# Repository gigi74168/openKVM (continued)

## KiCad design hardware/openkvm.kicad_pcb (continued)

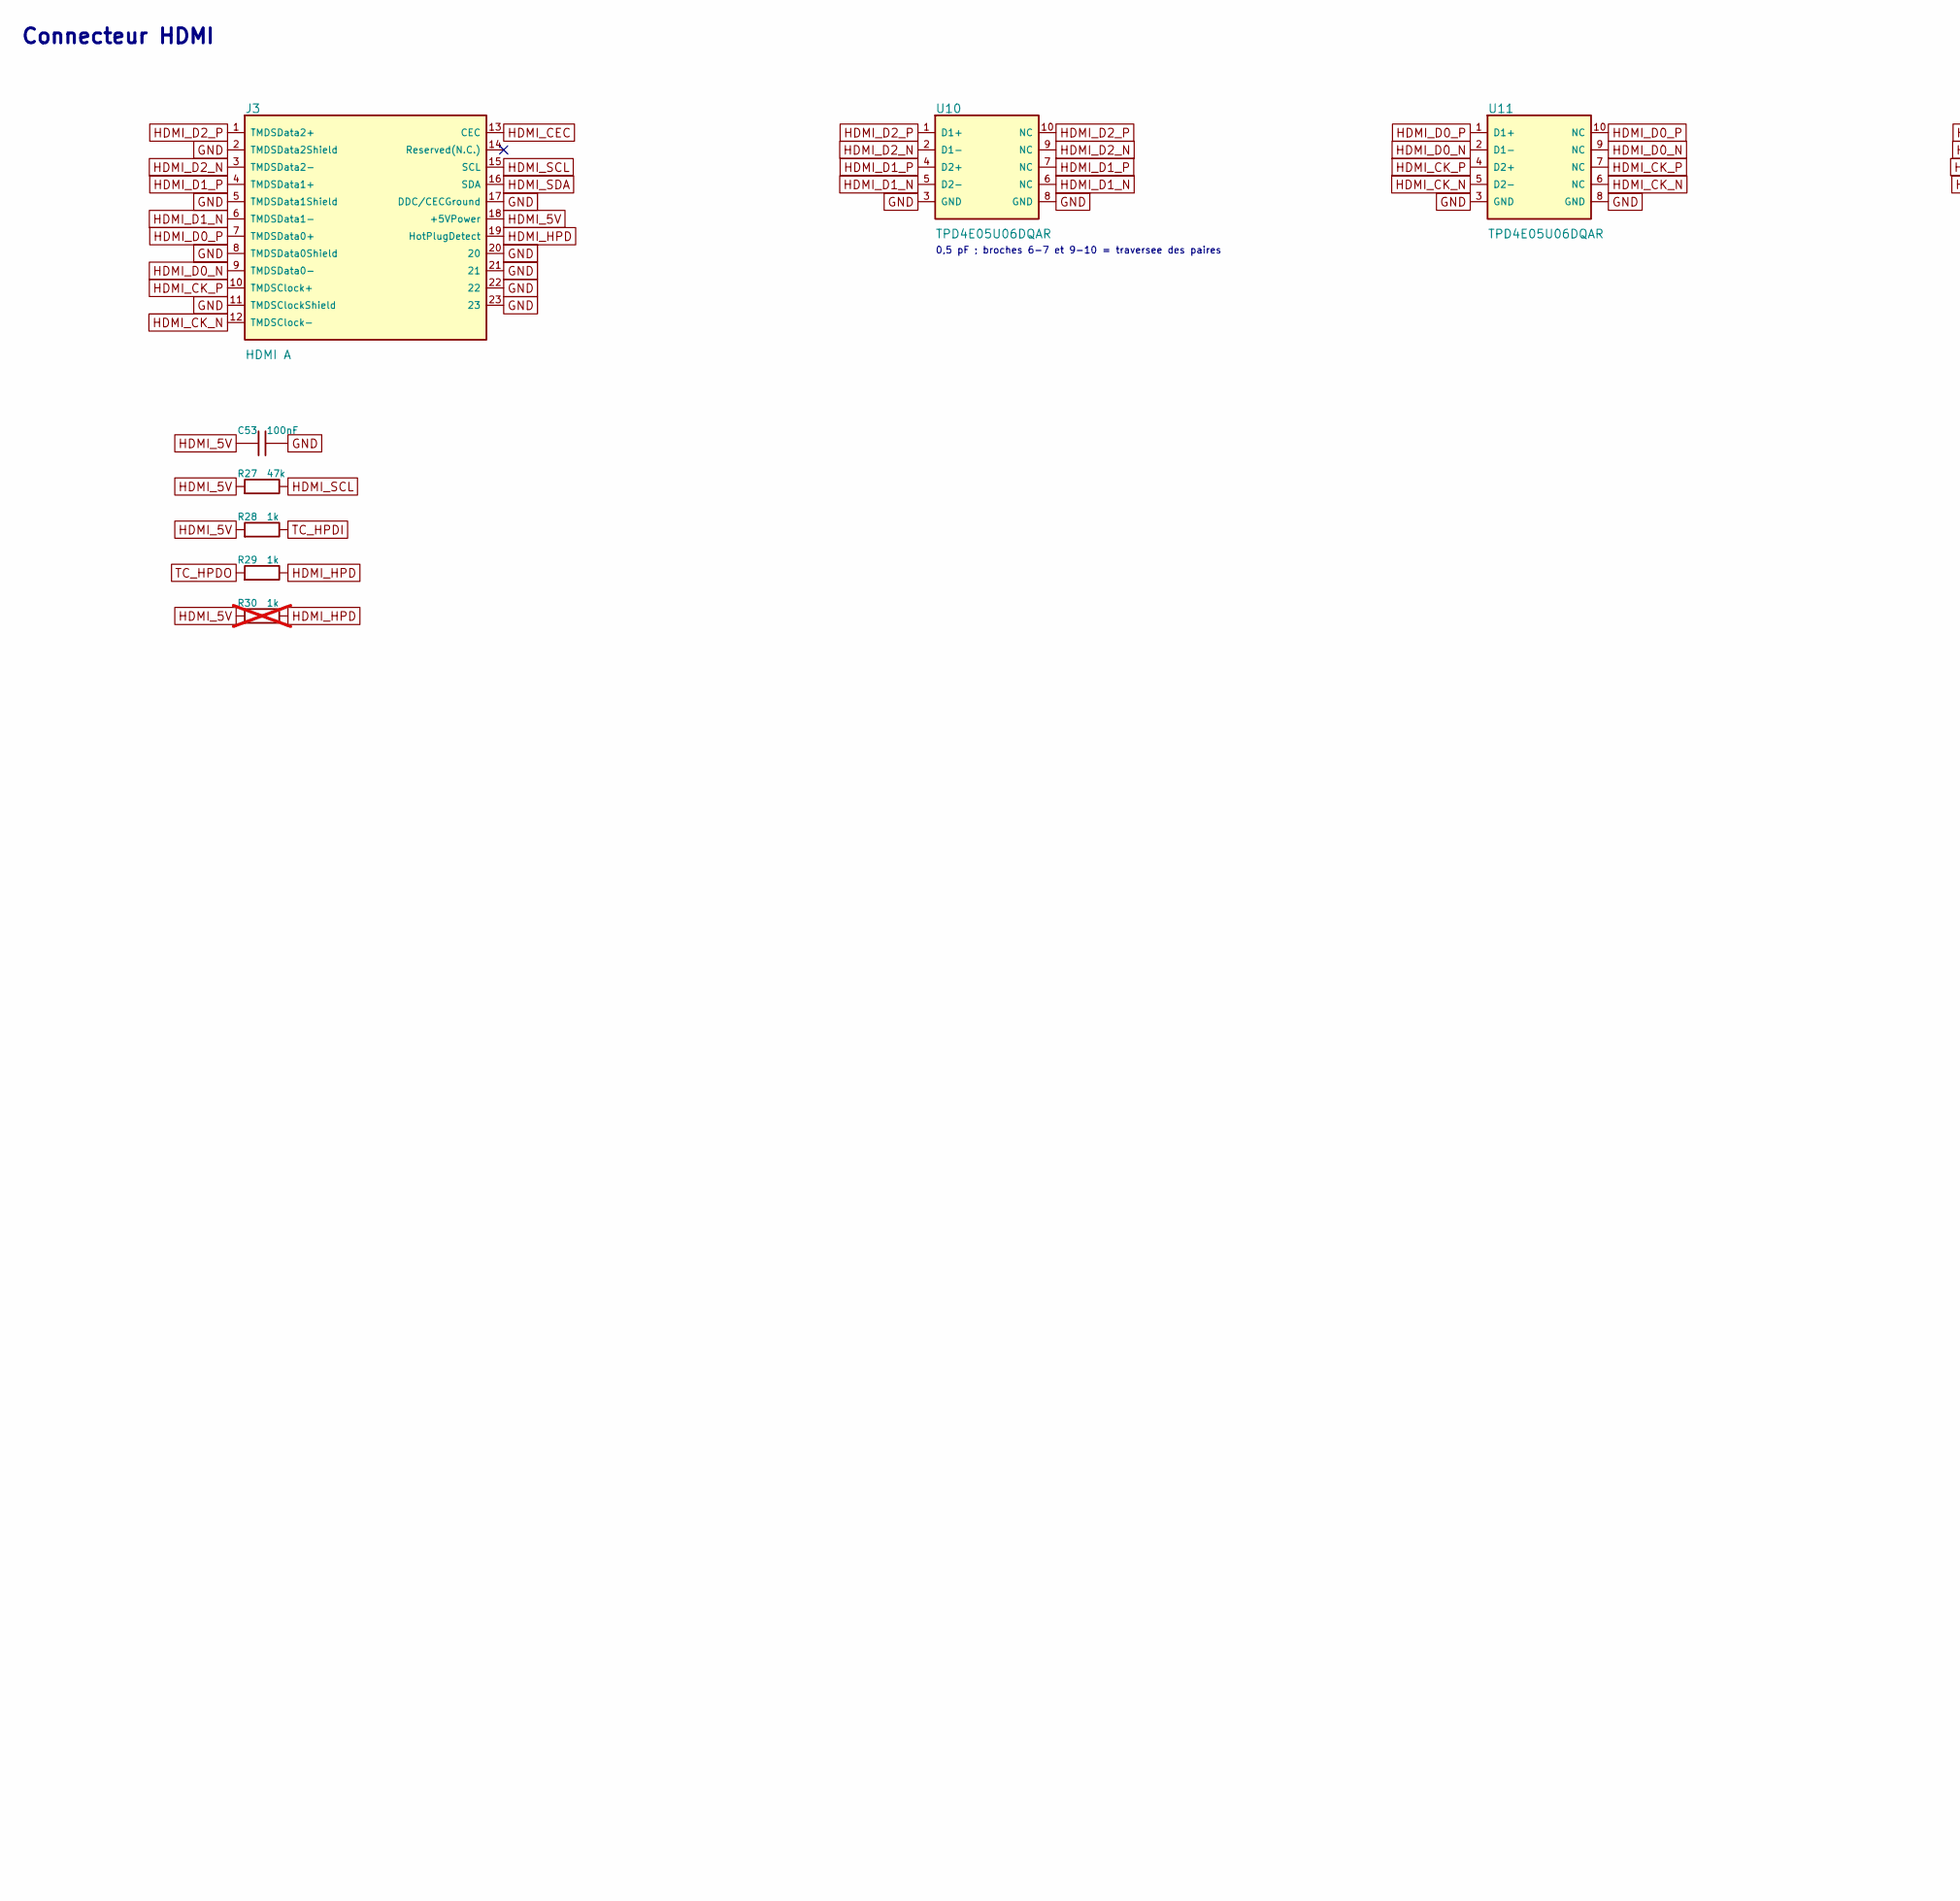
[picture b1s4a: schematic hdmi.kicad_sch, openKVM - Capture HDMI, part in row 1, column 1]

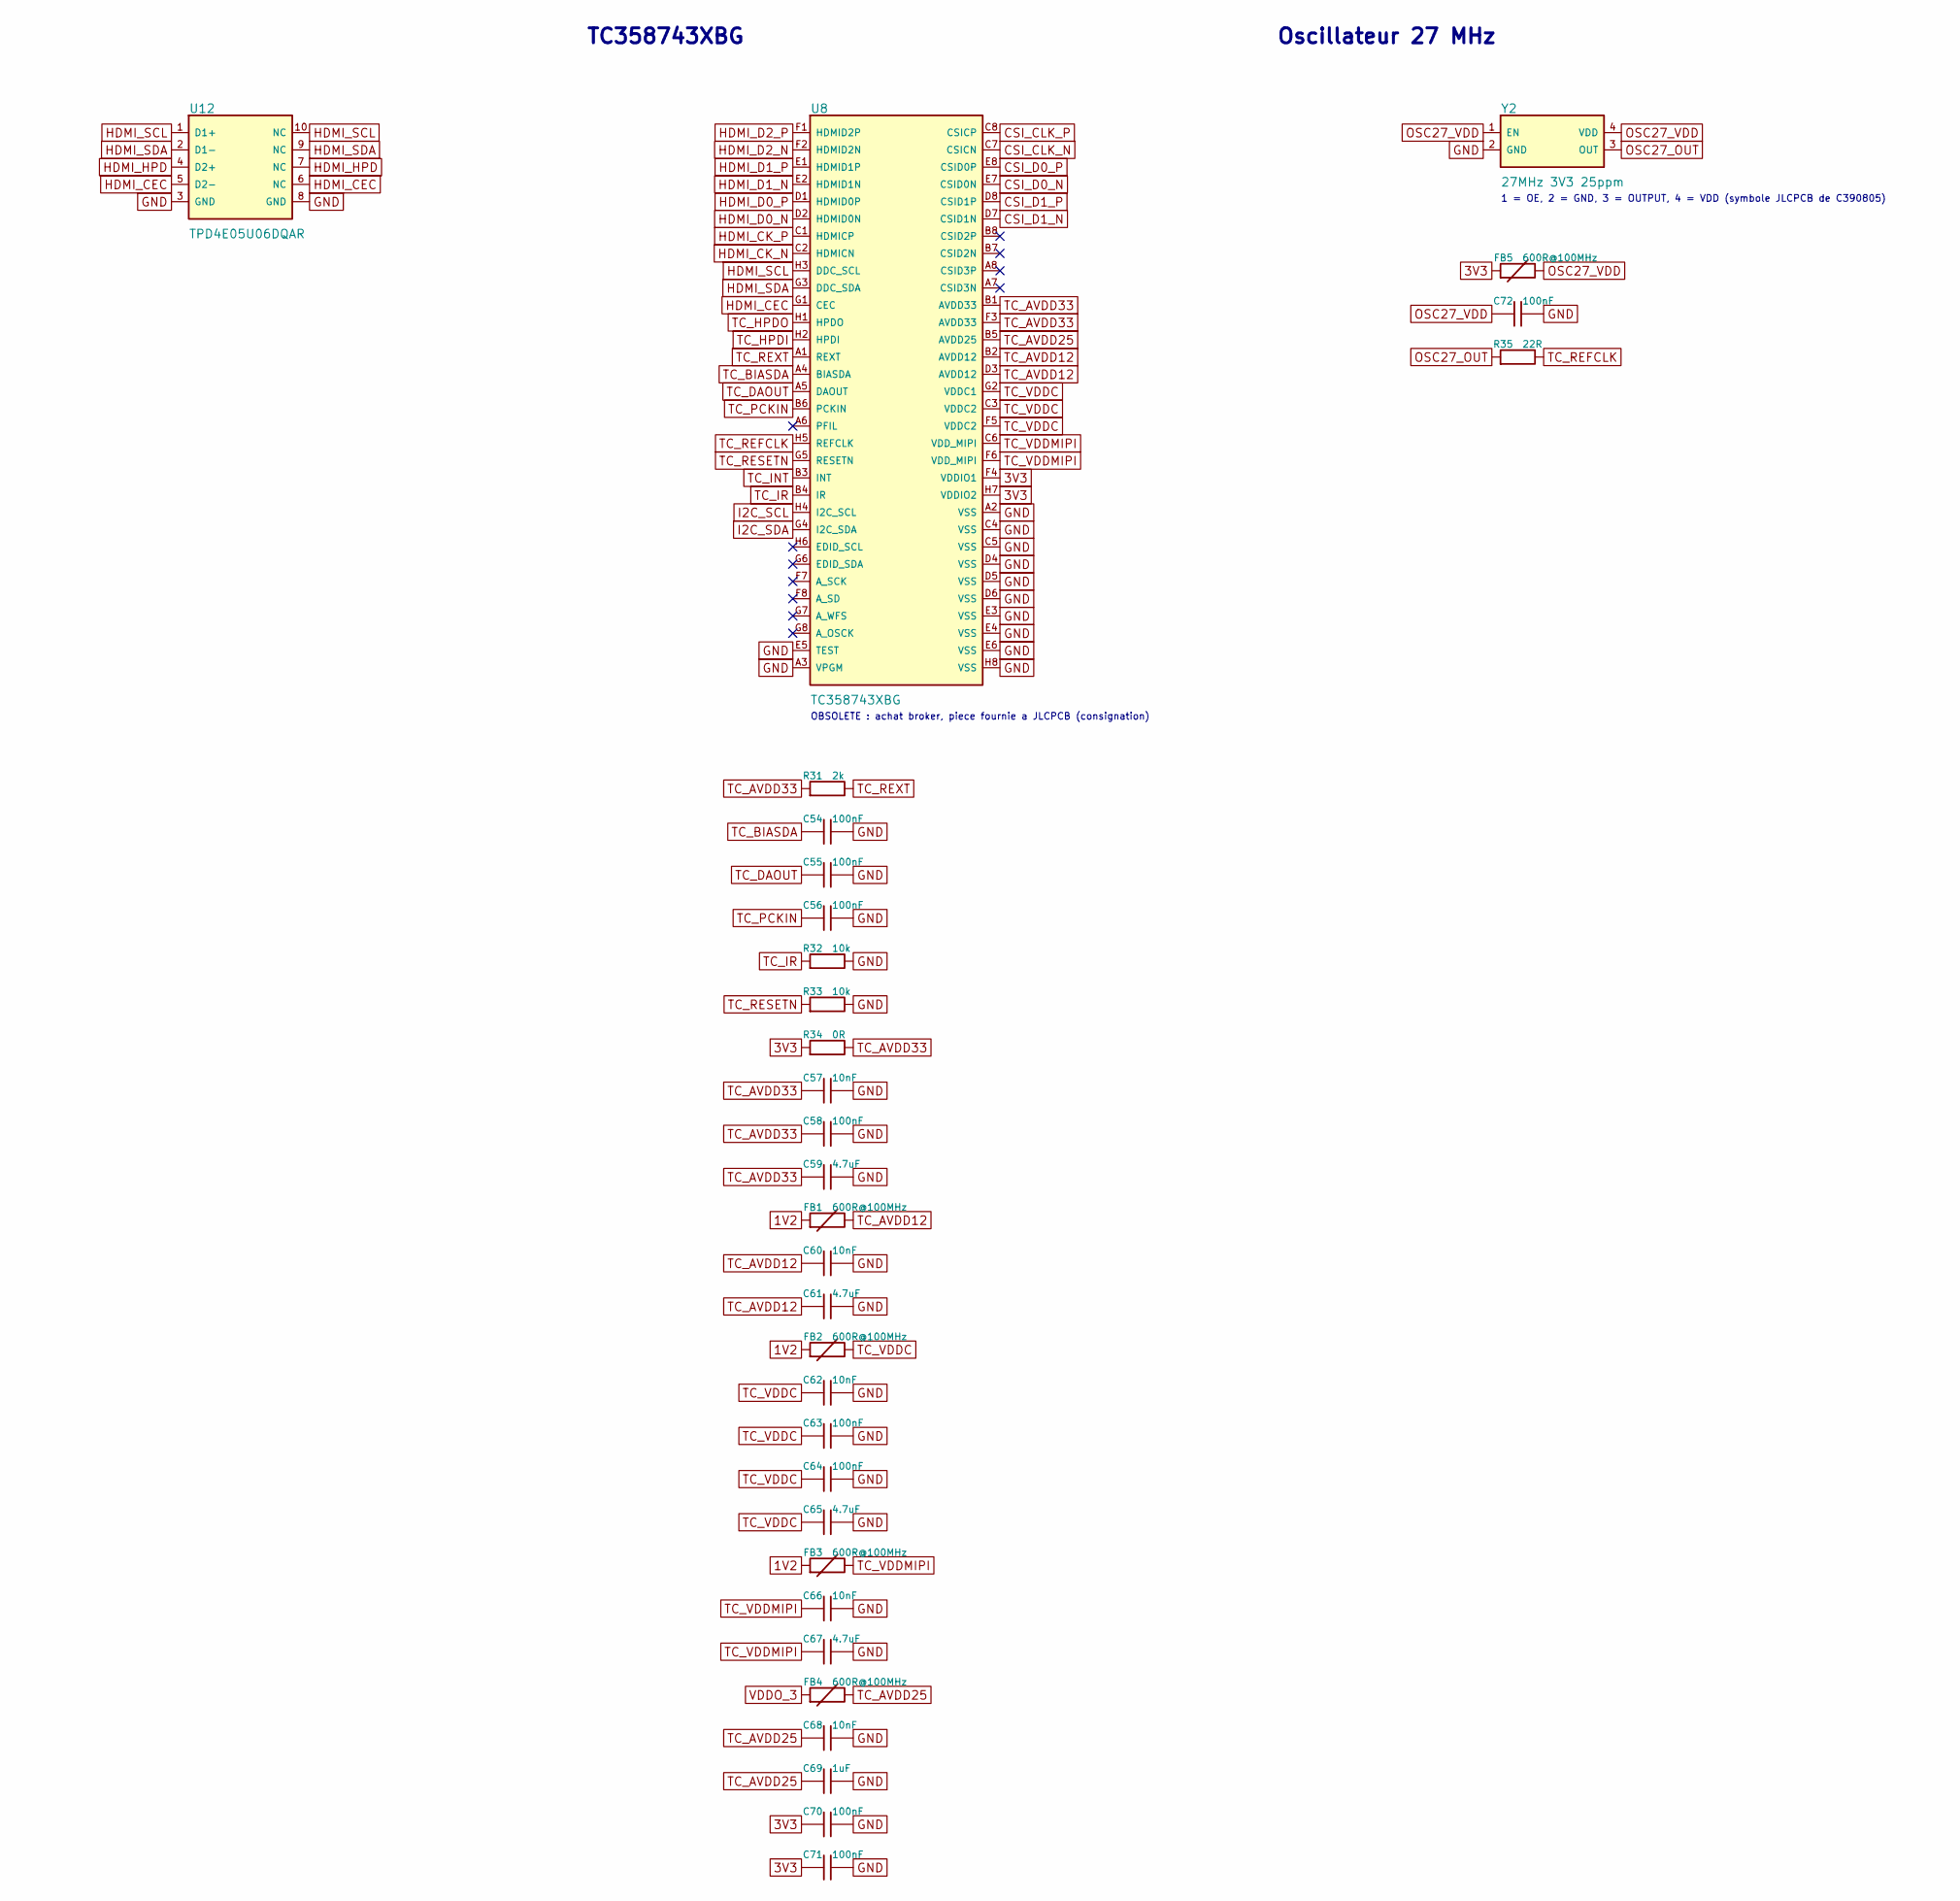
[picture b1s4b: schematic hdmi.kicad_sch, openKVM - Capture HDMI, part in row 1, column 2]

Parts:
C53, C54, C55, C56, C58, C63, C64, C70, C71, C72: 100nF; C_0402_1005Metric; MPN CL05B104KO5NNNC; LCSC C1525
C57, C60, C62, C66, C68: 10nF; C_0402_1005Metric; MPN CL05B103KB5NNNC; LCSC C15195
C59, C61, C65, C67: 4.7uF; C_0603_1608Metric; MPN CL10A475KO8NNNC; LCSC C19666
C69: 1uF; C_0402_1005Metric; MPN CL05A105KA5NQNC; LCSC C52923
FB1, FB2, FB3, FB4, FB5: 600R@100MHz; L_0603_1608Metric; MPN BLM18KG601SN1D; LCSC C85833
J3: HDMI A; HDMI-SMD_19P-P0.50-H-F; MPN HDMI-001 19PCBTP; LCSC C138388
R27: 47k; R_0402_1005Metric; MPN 0402WGF4702TCE; LCSC C25792
R28, R29: 1k; R_0402_1005Metric; MPN 0402WGF1001TCE; LCSC C11702
R30: 1k; R_0402_1005Metric; MPN 0402WGF1001TCE; LCSC C11702; not fitted
R31: 2k; R_0402_1005Metric; MPN 0402WGF2001TCE; LCSC C4109
R32, R33: 10k; R_0402_1005Metric; MPN 0402WGF1002TCE; LCSC C25744
R34: 0R; R_0402_1005Metric; MPN 0402WGF0000TCE; LCSC C17168
R35: 22R; R_0402_1005Metric; MPN 0402WGF220JTCE; LCSC C25092
U8: TC358743XBG; BGA-64_8x8_6.0x6.0mm; MPN TC358743XBG
U10, U11, U12: TPD4E05U06DQAR; USON-10_L2.5-W1.0-P0.50-BL; MPN TPD4E05U06DQAR; LCSC C138714
Y2: 27MHz 3V3 25ppm; OSC-SMD_4P-L3.2-W2.5-BL; MPN O3227000153350; LCSC C390805

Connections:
1V2: FB1.1, FB2.1, FB3.1; also elsewhere on the board
3V3: C70.1, C71.1, FB5.1, R34.1, U8.F4 (VDDIO1), U8.H7 (VDDIO2); also elsewhere on the board
CSI_CLK_N: U8.C7 (CSICN); also elsewhere on the board
CSI_CLK_P: U8.C8 (CSICP); also elsewhere on the board
CSI_D0_N: U8.E7 (CSID0N); also elsewhere on the board
CSI_D0_P: U8.E8 (CSID0P); also elsewhere on the board
CSI_D1_N: U8.D7 (CSID1N); also elsewhere on the board
CSI_D1_P: U8.D8 (CSID1P); also elsewhere on the board
GND: C53.2, C54.2, C55.2, C56.2, C57.2, C58.2, C59.2, C60.2, C61.2, C62.2, C63.2, C64.2, C65.2, C66.2, C67.2, C68.2, C69.2, C70.2, C71.2, C72.2, J3.2 (TMDSData2Shield), J3.5 (TMDSData1Shield), J3.8 (TMDSData0Shield), J3.11 (TMDSClockShield), J3.17 (DDC/CECGround), J3.20, J3.21, J3.22, J3.23, R32.2, R33.2, U8.A2 (VSS), U8.A3 (VPGM), U8.C4 (VSS), U8.C5 (VSS), U8.D4 (VSS), U8.D5 (VSS), U8.D6 (VSS), U8.E3 (VSS), U8.E4 (VSS), U8.E5 (TEST), U8.E6 (VSS), U8.H8 (VSS), U10.3 (GND), U10.8 (GND), U11.3 (GND), U11.8 (GND), U12.3 (GND), U12.8 (GND), Y2.2 (GND); also elsewhere on the board
HDMI_5V: C53.1, J3.18 (+5VPower), R27.1, R28.1, R30.1
HDMI_CEC: J3.13 (CEC), U8.G1 (CEC), U12.5 (D2-), U12.6 (NC)
HDMI_CK_N: J3.12 (TMDSClock-), U8.C2 (HDMICN), U11.5 (D2-), U11.6 (NC)
HDMI_CK_P: J3.10 (TMDSClock+), U8.C1 (HDMICP), U11.4 (D2+), U11.7 (NC)
HDMI_D0_N: J3.9 (TMDSData0-), U8.D2 (HDMID0N), U11.2 (D1-), U11.9 (NC)
HDMI_D0_P: J3.7 (TMDSData0+), U8.D1 (HDMID0P), U11.1 (D1+), U11.10 (NC)
HDMI_D1_N: J3.6 (TMDSData1-), U8.E2 (HDMID1N), U10.5 (D2-), U10.6 (NC)
HDMI_D1_P: J3.4 (TMDSData1+), U8.E1 (HDMID1P), U10.4 (D2+), U10.7 (NC)
HDMI_D2_N: J3.3 (TMDSData2-), U8.F2 (HDMID2N), U10.2 (D1-), U10.9 (NC)
HDMI_D2_P: J3.1 (TMDSData2+), U8.F1 (HDMID2P), U10.1 (D1+), U10.10 (NC)
HDMI_HPD: J3.19 (HotPlugDetect), R29.2, R30.2, U12.4 (D2+), U12.7 (NC)
HDMI_SCL: J3.15 (SCL), R27.2, U8.H3 (DDC_SCL), U12.1 (D1+), U12.10 (NC)
HDMI_SDA: J3.16 (SDA), U8.G3 (DDC_SDA), U12.2 (D1-), U12.9 (NC)
I2C_SCL: U8.H4 (I2C_SCL); also elsewhere on the board
I2C_SDA: U8.G4 (I2C_SDA); also elsewhere on the board
OSC27_OUT: R35.1, Y2.3 (OUT)
OSC27_VDD: C72.1, FB5.2, Y2.1 (EN), Y2.4 (VDD)
TC_AVDD12: C60.1, C61.1, FB1.2, U8.B2 (AVDD12), U8.D3 (AVDD12)
TC_AVDD25: C68.1, C69.1, FB4.2, U8.B5 (AVDD25)
TC_AVDD33: C57.1, C58.1, C59.1, R31.1, R34.2, U8.B1 (AVDD33), U8.F3 (AVDD33)
TC_BIASDA: C54.1, U8.A4 (BIASDA)
TC_DAOUT: C55.1, U8.A5 (DAOUT)
TC_HPDI: R28.2, U8.H2 (HPDI)
TC_HPDO: R29.1, U8.H1 (HPDO)
TC_INT: U8.B3 (INT); also elsewhere on the board
TC_IR: R32.1, U8.B4 (IR)
TC_PCKIN: C56.1, U8.B6 (PCKIN)
TC_REFCLK: R35.2, U8.H5 (REFCLK)
TC_RESETN: R33.1, U8.G5 (RESETN); also elsewhere on the board
TC_REXT: R31.2, U8.A1 (REXT)
TC_VDDC: C62.1, C63.1, C64.1, C65.1, FB2.2, U8.C3 (VDDC2), U8.F5 (VDDC2), U8.G2 (VDDC1)
TC_VDDMIPI: C66.1, C67.1, FB3.2, U8.C6 (VDD_MIPI), U8.F6 (VDD_MIPI)
VDDO_3: FB4.1; also elsewhere on the board

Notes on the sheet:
Connecteur HDMI
0,5 pF ; broches 6-7 et 9-10 = traversee des paires
TC358743XBG
OBSOLETE : achat broker, piece fournie a JLCPCB (consignation)
Oscillateur 27 MHz
1 = OE, 2 = GND, 3 = OUTPUT, 4 = VDD (symbole JLCPCB de C390805)

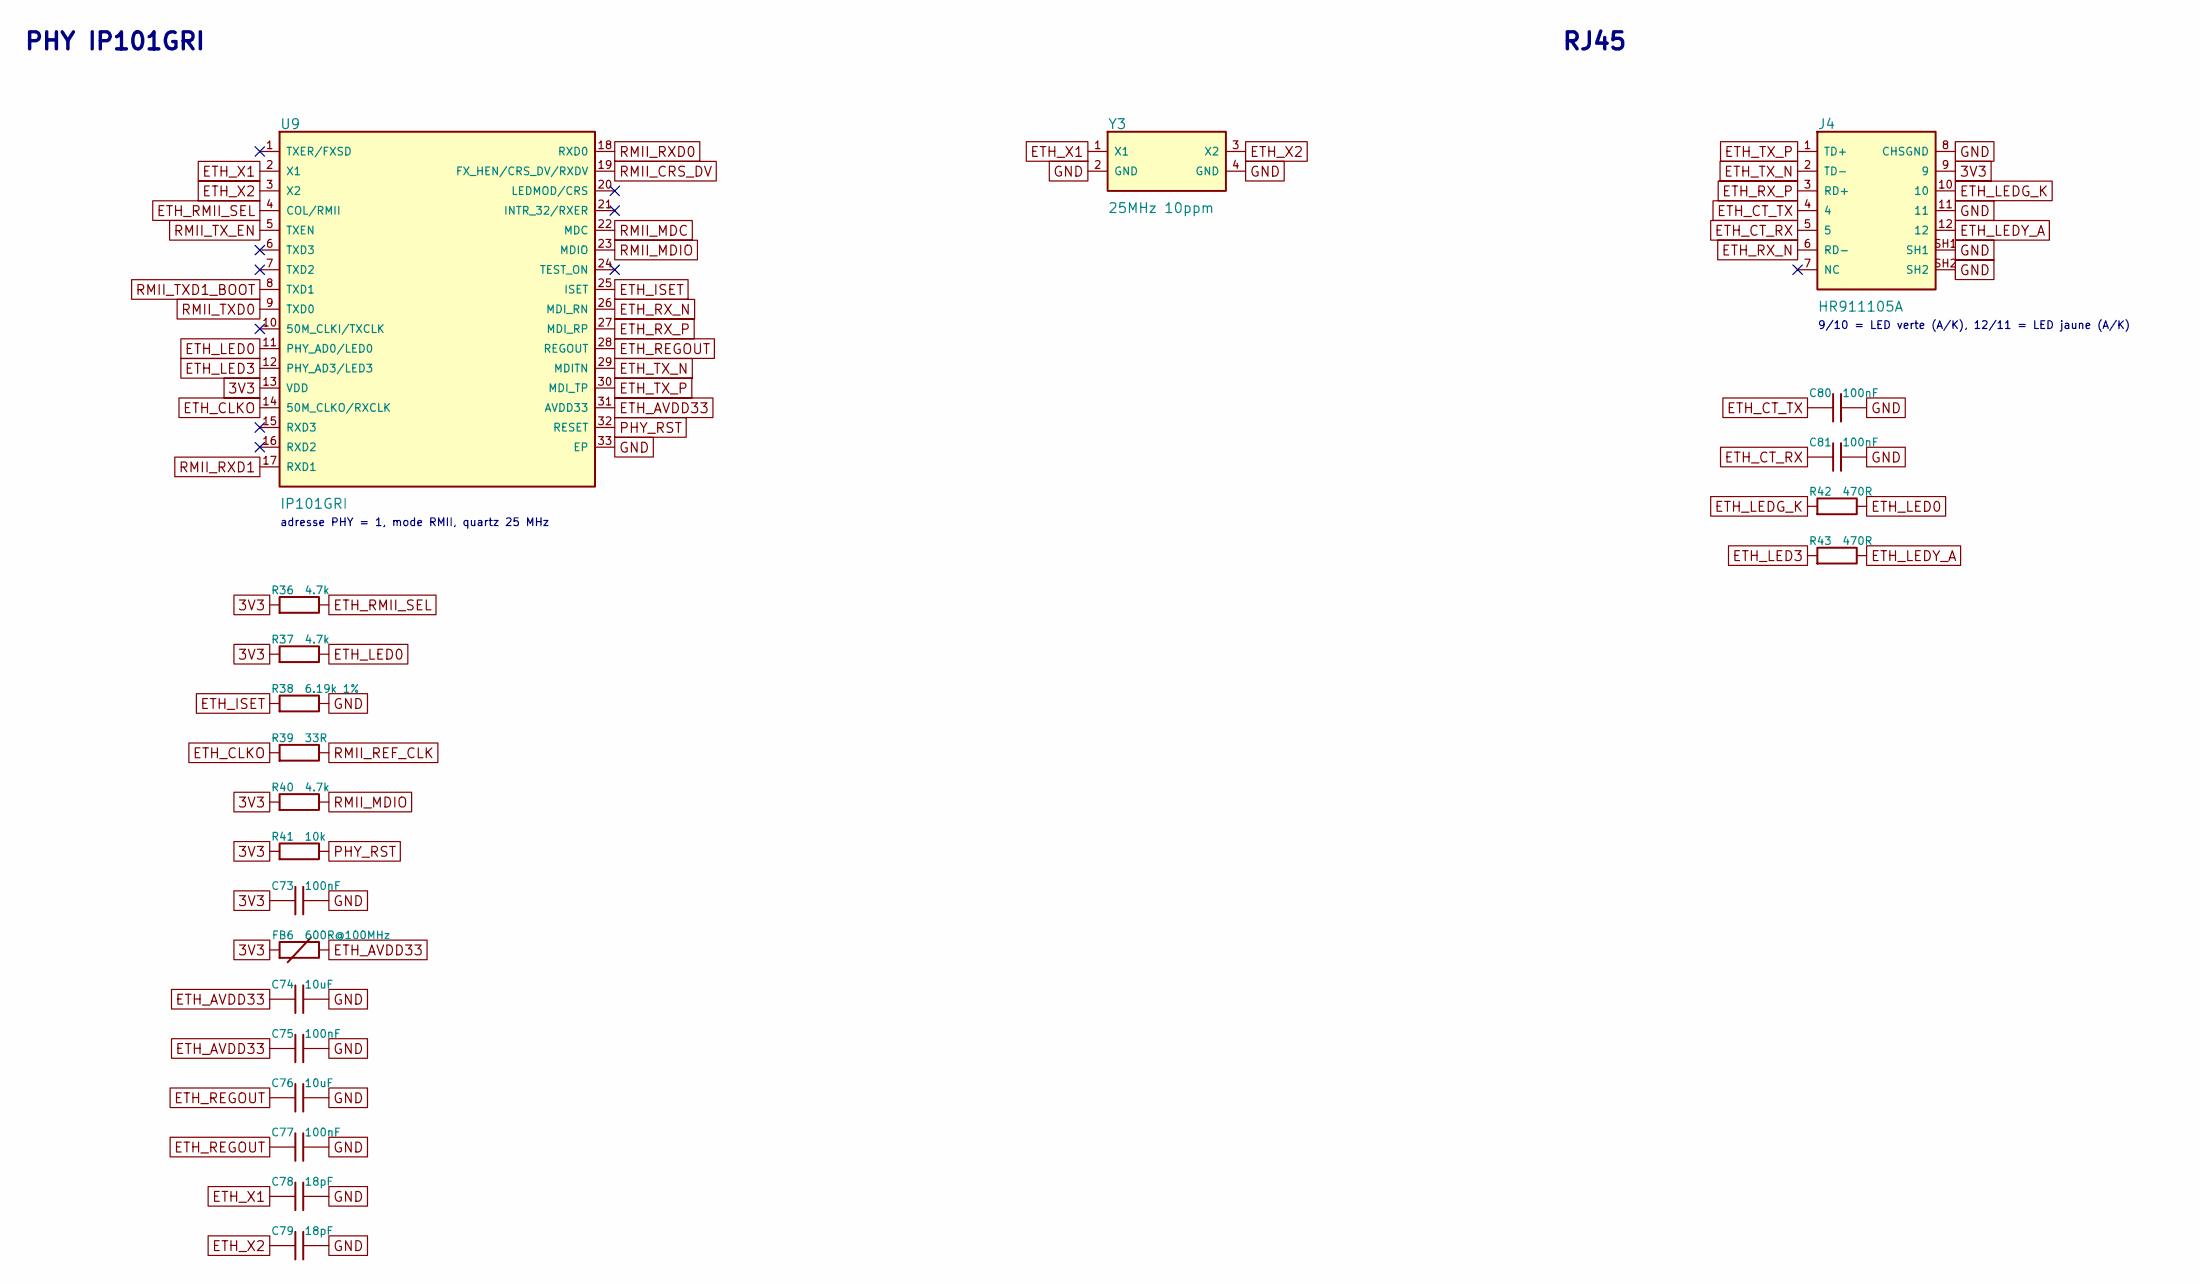
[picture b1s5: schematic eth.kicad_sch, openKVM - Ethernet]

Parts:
C73, C75, C77, C80, C81: 100nF; C_0402_1005Metric; MPN CL05B104KO5NNNC; LCSC C1525
C74, C76: 10uF; C_0603_1608Metric; MPN CL10A106KP8NNNC; LCSC C19702
C78, C79: 18pF; C_0402_1005Metric; MPN 0402CG180J500NT; LCSC C1549
FB6: 600R@100MHz; L_0603_1608Metric; MPN BLM18KG601SN1D; LCSC C85833
J4: HR911105A; RJ45-TH_HR911105A; MPN HR911105A; LCSC C12074
R36, R37, R40: 4.7k; R_0402_1005Metric; MPN 0402WGF4701TCE; LCSC C25900
R38: 6.19k 1%; R_0402_1005Metric; MPN 0402WGF6191TCE; LCSC C25914
R39: 33R; R_0402_1005Metric; MPN 0402WGF330JTCE; LCSC C25105
R41: 10k; R_0402_1005Metric; MPN 0402WGF1002TCE; LCSC C25744
R42, R43: 470R; R_0402_1005Metric; MPN 0402WGF4700TCE; LCSC C25117
U9: IP101GRI; QFN-32_L4.0-W4.0-P0.40-BL-EP2.7; MPN IP101GRI; LCSC C703537
Y3: 25MHz 10ppm; CRYSTAL-SMD_4P-L3.2-W2.5-BL; MPN X322525MOB4SI; LCSC C9006

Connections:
3V3: C73.1, FB6.1, J4.9, R36.1, R37.1, R40.1, R41.1, U9.13 (VDD); also elsewhere on the board
ETH_AVDD33: C74.1, C75.1, FB6.2, U9.31 (AVDD33)
ETH_CLKO: R39.1, U9.14 (50M_CLKO/RXCLK)
ETH_CT_RX: C81.1, J4.5
ETH_CT_TX: C80.1, J4.4
ETH_ISET: R38.1, U9.25 (ISET)
ETH_LED0: R37.2, R42.2, U9.11 (PHY_AD0/LED0)
ETH_LED3: R43.1, U9.12 (PHY_AD3/LED3)
ETH_LEDG_K: J4.10, R42.1
ETH_LEDY_A: J4.12, R43.2
ETH_REGOUT: C76.1, C77.1, U9.28 (REGOUT)
ETH_RMII_SEL: R36.2, U9.4 (COL/RMII)
ETH_RX_N: J4.6 (RD-), U9.26 (MDI_RN)
ETH_RX_P: J4.3 (RD+), U9.27 (MDI_RP)
ETH_TX_N: J4.2 (TD-), U9.29 (MDITN)
ETH_TX_P: J4.1 (TD+), U9.30 (MDI_TP)
ETH_X1: C78.1, U9.2 (X1), Y3.1 (X1)
ETH_X2: C79.1, U9.3 (X2), Y3.3 (X2)
GND: C73.2, C74.2, C75.2, C76.2, C77.2, C78.2, C79.2, C80.2, C81.2, J4.8 (CHSGND), J4.11, J4.SH1, J4.SH2, R38.2, U9.33 (EP), Y3.2 (GND), Y3.4 (GND); also elsewhere on the board
PHY_RST: R41.2, U9.32 (RESET); also elsewhere on the board
RMII_CRS_DV: U9.19 (FX_HEN/CRS_DV/RXDV); also elsewhere on the board
RMII_MDC: U9.22 (MDC); also elsewhere on the board
RMII_MDIO: R40.2, U9.23 (MDIO); also elsewhere on the board
RMII_REF_CLK: R39.2; also elsewhere on the board
RMII_RXD0: U9.18 (RXD0); also elsewhere on the board
RMII_RXD1: U9.17 (RXD1); also elsewhere on the board
RMII_TXD0: U9.9 (TXD0); also elsewhere on the board
RMII_TXD1_BOOT: U9.8 (TXD1); also elsewhere on the board
RMII_TX_EN: U9.5 (TXEN); also elsewhere on the board

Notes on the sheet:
PHY IP101GRI
adresse PHY = 1, mode RMII, quartz 25 MHz
RJ45
9/10 = LED verte (A/K), 12/11 = LED jaune (A/K)

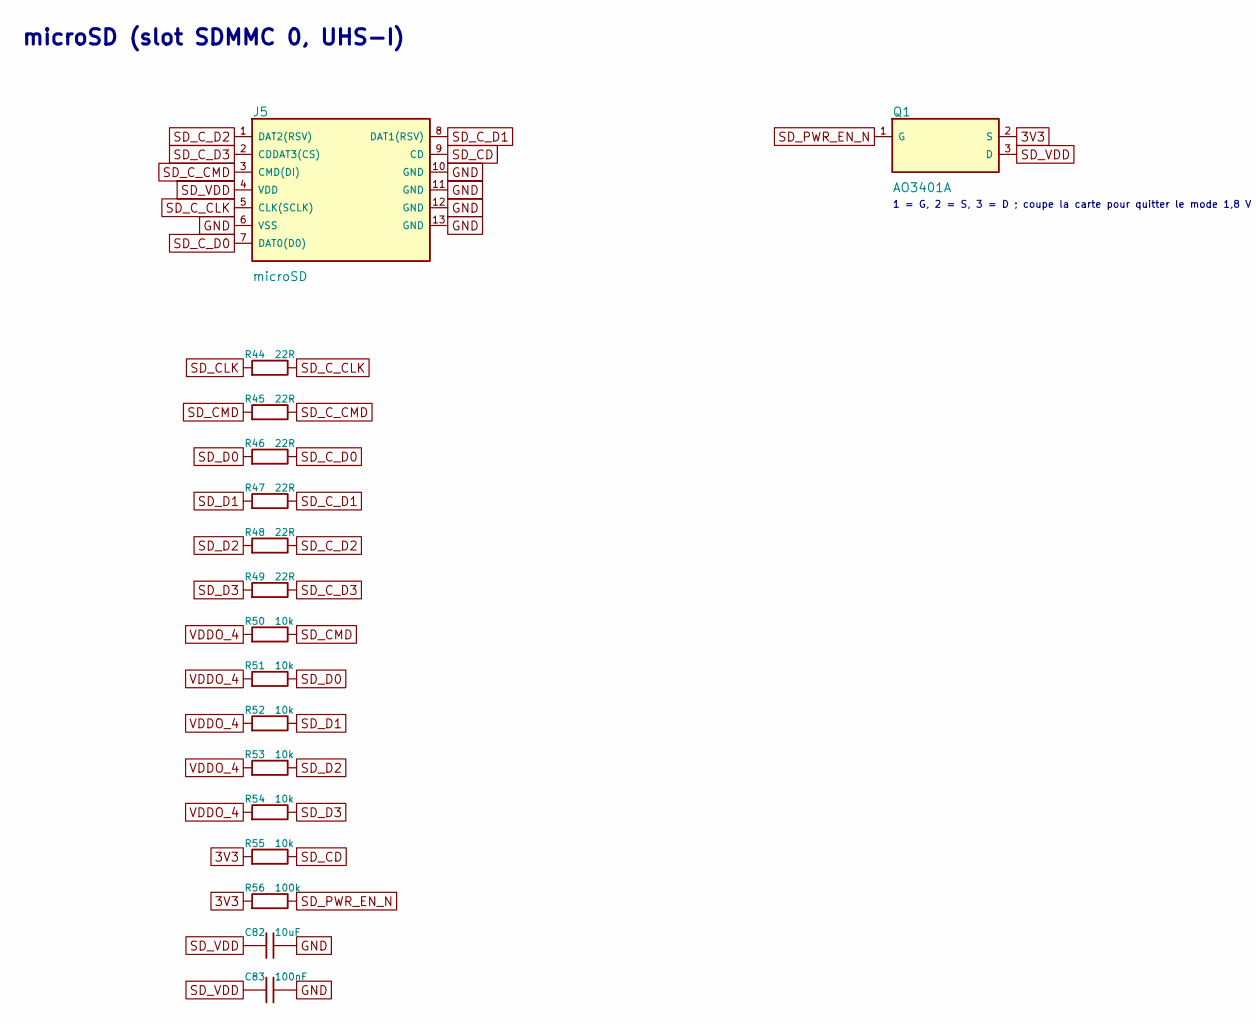
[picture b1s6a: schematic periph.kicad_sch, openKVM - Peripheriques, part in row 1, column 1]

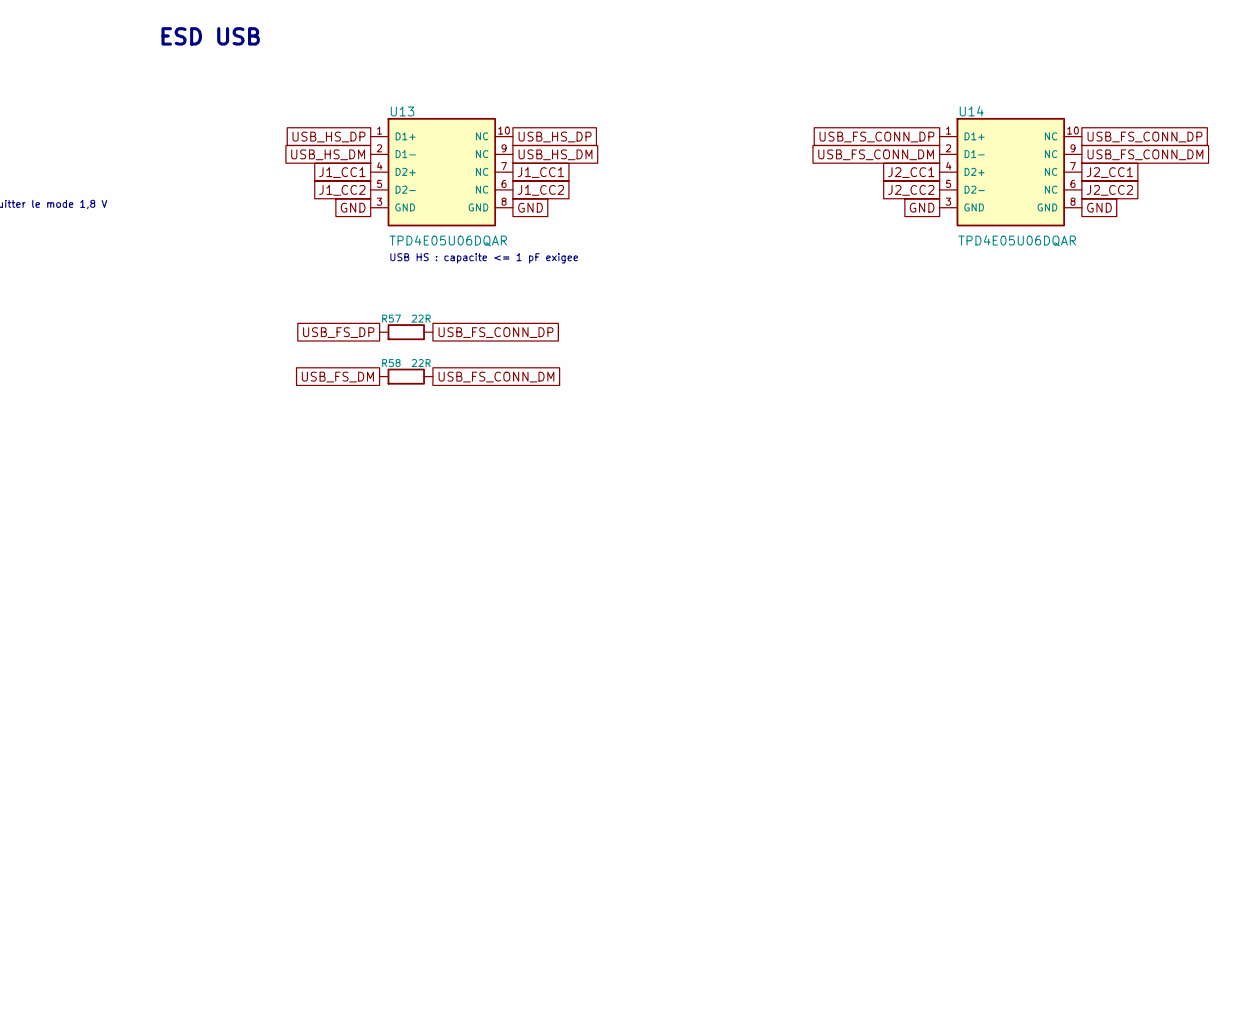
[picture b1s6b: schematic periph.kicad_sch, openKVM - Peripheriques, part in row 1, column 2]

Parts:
C82: 10uF; C_0603_1608Metric; MPN CL10A106KP8NNNC; LCSC C19702
C83: 100nF; C_0402_1005Metric; MPN CL05B104KO5NNNC; LCSC C1525
J5: microSD; TF-SMD_TF-01A; MPN TF-01A; LCSC C91145
Q1: AO3401A; SOT-23_L2.9-W1.3-P1.90-LS2.4-BR; MPN AO3401A; LCSC C15127
R44, R45, R46, R47, R48, R49, R57, R58: 22R; R_0402_1005Metric; MPN 0402WGF220JTCE; LCSC C25092
R50, R51, R52, R53, R54, R55: 10k; R_0402_1005Metric; MPN 0402WGF1002TCE; LCSC C25744
R56: 100k; R_0402_1005Metric; MPN 0402WGF1003TCE; LCSC C25741
U13, U14: TPD4E05U06DQAR; USON-10_L2.5-W1.0-P0.50-BL; MPN TPD4E05U06DQAR; LCSC C138714

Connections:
3V3: Q1.2 (S), R55.1, R56.1; also elsewhere on the board
GND: C82.2, C83.2, J5.6 (VSS), J5.10 (GND), J5.11 (GND), J5.12 (GND), J5.13 (GND), U13.3 (GND), U13.8 (GND), U14.3 (GND), U14.8 (GND); also elsewhere on the board
J1_CC1: U13.4 (D2+), U13.7 (NC); also elsewhere on the board
J1_CC2: U13.5 (D2-), U13.6 (NC); also elsewhere on the board
J2_CC1: U14.4 (D2+), U14.7 (NC); also elsewhere on the board
J2_CC2: U14.5 (D2-), U14.6 (NC); also elsewhere on the board
SD_CD: J5.9 (CD), R55.2; also elsewhere on the board
SD_CLK: R44.1; also elsewhere on the board
SD_CMD: R45.1, R50.2; also elsewhere on the board
SD_C_CLK: J5.5 (CLK(SCLK)), R44.2
SD_C_CMD: J5.3 (CMD(DI)), R45.2
SD_C_D0: J5.7 (DAT0(D0)), R46.2
SD_C_D1: J5.8 (DAT1(RSV)), R47.2
SD_C_D2: J5.1 (DAT2(RSV)), R48.2
SD_C_D3: J5.2 (CDDAT3(CS)), R49.2
SD_D0: R46.1, R51.2; also elsewhere on the board
SD_D1: R47.1, R52.2; also elsewhere on the board
SD_D2: R48.1, R53.2; also elsewhere on the board
SD_D3: R49.1, R54.2; also elsewhere on the board
SD_PWR_EN_N: Q1.1 (G), R56.2; also elsewhere on the board
SD_VDD: C82.1, C83.1, J5.4 (VDD), Q1.3 (D)
USB_FS_CONN_DM: R58.2, U14.2 (D1-), U14.9 (NC); also elsewhere on the board
USB_FS_CONN_DP: R57.2, U14.1 (D1+), U14.10 (NC); also elsewhere on the board
USB_FS_DM: R58.1; also elsewhere on the board
USB_FS_DP: R57.1; also elsewhere on the board
USB_HS_DM: U13.2 (D1-), U13.9 (NC); also elsewhere on the board
USB_HS_DP: U13.1 (D1+), U13.10 (NC); also elsewhere on the board
VDDO_4: R50.1, R51.1, R52.1, R53.1, R54.1; also elsewhere on the board

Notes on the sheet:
microSD (slot SDMMC 0, UHS-I)
1 = G, 2 = S, 3 = D ; coupe la carte pour quitter le mode 1,8 V
ESD USB
USB HS : capacite <= 1 pF exigee

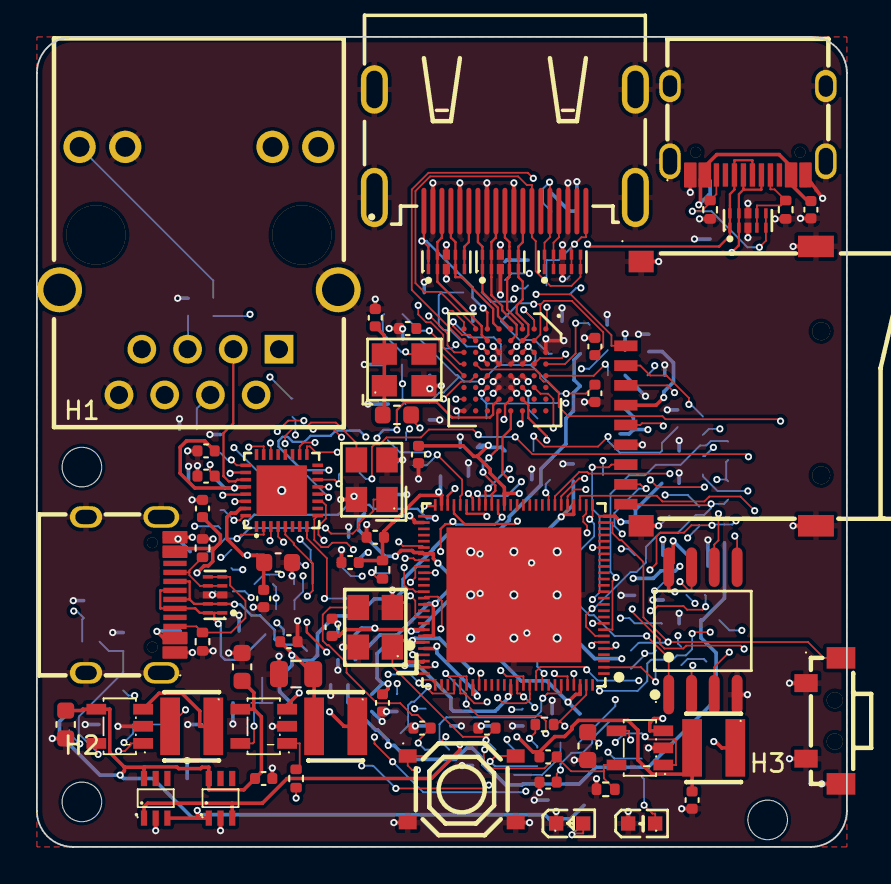
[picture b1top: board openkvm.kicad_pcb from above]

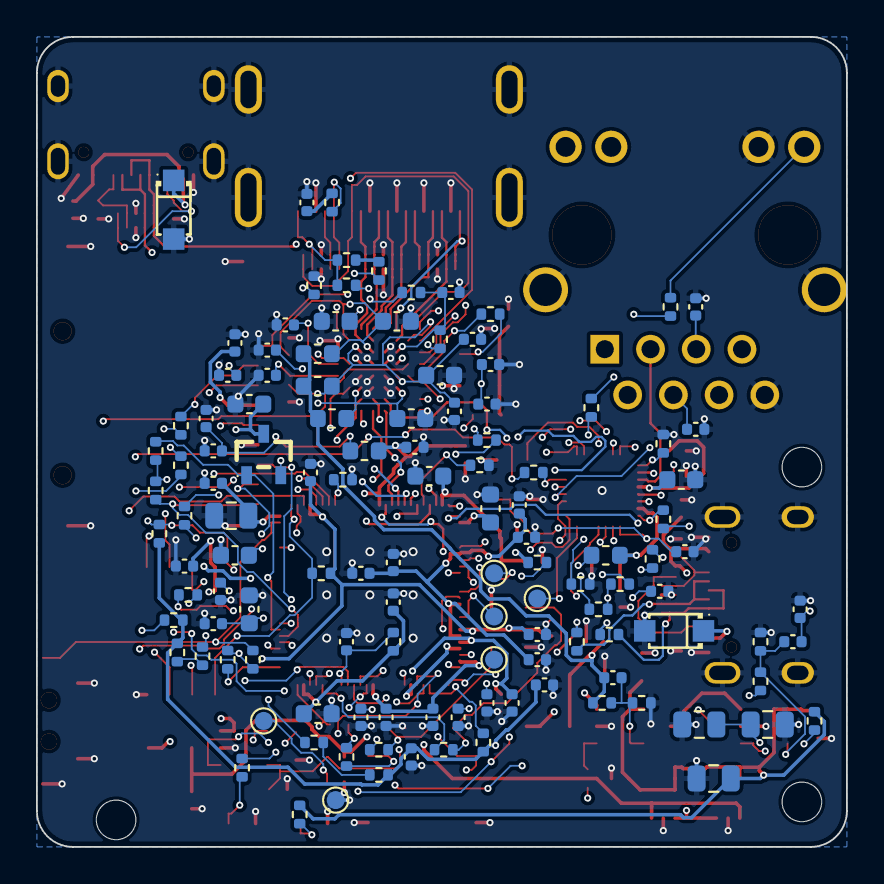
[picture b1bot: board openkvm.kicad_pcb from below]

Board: 4 copper layers, 45.0 x 45.0 mm, 188 parts (121 on the bottom side), 131 nets.

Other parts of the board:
H1, H2, H3: MountingHole_2.2mm_M2

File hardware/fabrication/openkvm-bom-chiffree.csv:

Comment,Designator,LCSC Part #,MPN,Qty/carte,Biblio JLCPCB,Stock JLCPCB,Qte commandee (8 cartes),Prix unitaire USD,Cout ligne USD,Cout/carte USD,Prix lu le
100nF,"C1,C2,C4,C9,C13,C15,C16,C17,C18,C19,C21,C23,C25,C28,C29,C30,C31,C34,C37,C39,C42,C45,C51,C53,C54,C55,C56,C58,C63,C64,C70,C71,C72,C73,C75,C77,C80,C81,C83",C1525,CL05B104KO5NNNC,39,base,33122364,327,0.0029,0.9483,0.1185,2026-11-12
22uF,"C3,C7,C8,C12,C48",C45783,CL21A226MAQNNNE,5,base,4351184,44,0.1055,4.6420,0.5802,2026-11-12
22pF,"C5,C10,C46,C49,C50",C1555,0402CG220J500NT,5,base,1486200,50,0.0019,0.0950,0.0119,2026-11-12
10uF,"C6,C11,C14,C20,C22,C27,C74,C76,C82",C19702,CL10A106KP8NNNC,9,base,9806517,82,0.0233,1.9106,0.2388,2026-11-12
10nF,"C24,C41,C57,C60,C62,C66,C68",C15195,CL05B103KB5NNNC,7,base,5551962,71,0.0037,0.2627,0.0328,2026-11-12
4.7uF,"C26,C47,C59,C61,C65,C67",C19666,CL10A475KO8NNNC,6,base,3674286,58,0.015,0.8700,0.1087,2026-11-12
1uF,"C32,C33,C35,C36,C38,C40,C43,C44,C52,C69",C52923,CL05A105KA5NQNC,10,base,10648463,92,0.0057,0.5244,0.0655,2026-11-12
18pF,"C78,C79",C1549,0402CG180J500NT,2,base,1012812,26,0.0018,0.0468,0.0059,2026-11-12
SMF5.0A,"D1,D2",C19077497,SMF5.0A,2,expand,814136,20,0.0283,0.5660,0.0707,2026-11-12
LED jaune etat,D3,C2287,KT-0603Y,1,expand,64642,22,0.0106,0.2332,0.0291,2026-11-12
LED verte alim,D4,C12624,KT-0603G,1,expand,272298,24,0.0119,0.2856,0.0357,2026-11-12
600R@100MHz,"FB1,FB2,FB3,FB4,FB5,FB6",C85833,BLM18KG601SN1D,6,expand,762635,58,0.0172,0.9976,0.1247,2026-11-12
USB-C CIBLE,J1,C165948,TYPE-C-31-M-12,1,expand,544123,8,0.1868,1.4944,0.1868,2026-11-12
USB-C EXT,J2,C165948,TYPE-C-31-M-12,1,expand,544123,8,0.1868,1.4944,0.1868,2026-11-12
HDMI A,J3,C138388,HDMI-001 19PCBTP,1,expand,20938,8,0.2294,1.8352,0.2294,2026-11-12
HR911105A,J4,C12074,HR911105A,1,expand,52499,8,1.724,13.7920,1.7240,2026-11-12
microSD,J5,C91145,TF-01A,1,expand,135927,9,0.1931,1.7379,0.2172,2026-11-12
2.2uH 2A,"L1,L2,L3",C43389,SWPA3015S2R2MT,3,expand,35596,28,0.0437,1.2236,0.1530,2026-11-12
AO3401A,Q1,C15127,AO3401A,1,base,1628648,12,0.0813,0.9756,0.1220,2026-11-12
5.1k,"R1,R2,R3,R4",C25905,0402WGF5101TCE,4,base,4063573,47,0.0014,0.0658,0.0082,2026-11-12
100k,"R5,R6,R8,R9,R10,R56",C25741,0402WGF1003TCE,6,base,8795458,60,0.0011,0.0660,0.0083,2026-11-12
22k,R7,C25768,0402WGF2202TCE,1,base,1355879,20,0.001,0.0200,0.0025,2026-11-12
0R,"R11,R12,R17,R18,R34",C17168,0402WGF0000TCE,5,base,15994928,50,0.0012,0.0600,0.0075,2026-11-12
4.02k 1%,"R13,R14",C43251,0402WGF4021TCE,2,expand,735329,26,0.0013,0.0338,0.0042,2026-11-12
499k 1%,"R15,R16",C25793,0402WGF4993TCE,2,expand,97503,26,0.0032,0.0832,0.0104,2026-11-12
10k,"R19,R20,R21,R23,R32,R33,R41,R50,R51,R52,R53,R54,R55",C25744,0402WGF1002TCE,13,base,22059957,119,0.001,0.1190,0.0149,2026-11-12
1k,"R22,R28,R29",C11702,0402WGF1001TCE,3,base,31989961,34,0.0013,0.0442,0.0055,2026-11-12
470R,"R24,R42,R43",C25117,0402WGF4700TCE,3,base,2720105,34,0.001,0.0340,0.0043,2026-11-12
4.7k,"R25,R26,R36,R37,R40",C25900,0402WGF4701TCE,5,base,14673672,50,0.0017,0.0850,0.0106,2026-11-12
47k,R27,C25792,0402WGF4702TCE,1,base,5793558,20,0.0019,0.0380,0.0047,2026-11-12
2k,R31,C4109,0402WGF2001TCE,1,base,10181133,20,0.0019,0.0380,0.0047,2026-11-12
22R,"R35,R44,R45,R46,R47,R48,R49,R57,R58",C25092,0402WGF220JTCE,9,base,4915708,87,0.0033,0.2871,0.0359,2026-11-12
6.19k 1%,R38,C25914,0402WGF6191TCE,1,expand,112984,20,0.0012,0.0240,0.0030,2026-11-12
33R,R39,C25105,0402WGF330JTCE,1,base,3584572,23,0.0011,0.0253,0.0032,2026-11-12
FN,SW1,C318936,TS-1101VS-C-A-A,1,expand,3508,14,0.082,1.1480,0.1435,2026-11-12
BOOT,SW2,C318884,TS-1187A-B-A-B,1,base,827927,16,0.0215,0.3440,0.0430,2026-11-12
ESP32-P4NRW32X,U1,C54540373,ESP32-P4NRW32X,1,expand,203,8,6.1467,49.1736,6.1467,2026-11-12
TLV62569DBVR,"U2,U5,U6",C141836,TLV62569DBVR,3,expand,645436,28,0.0674,1.8872,0.2359,2026-11-12
LM66100DCKR,"U3,U4",C2869734,LM66100DCKR,2,expand,44098,16,0.1949,3.1184,0.3898,2026-11-12
GD25Q128ESIGR,U7,C2928891,GD25Q128ESIGR,1,expand,1085,8,1.4214,11.3712,1.4214,2026-11-12
TC358743XBG,U8,,TC358743XBG,1,,,,A DEVIS (broker),,,
IP101GRI,U9,C703537,IP101GRI,1,expand,17717,8,1.0256,8.2048,1.0256,2026-11-12
TPD4E05U06DQAR,"U10,U11,U12,U13,U14",C138714,TPD4E05U06DQAR,5,expand,4535,44,0.0835,3.6740,0.4593,2026-11-12
40MHz 10ppm,Y1,C9010,X322540MPB4SI,1,expand,54447,12,0.1093,1.3116,0.1639,2026-11-12
27MHz 3V3 HCMOS,Y2,C2992365,CO32H4-27.000-33JDTSNL,1,expand,27,8,0.4041,3.2328,0.4041,2026-11-12
25MHz 10ppm,Y3,C9006,X322525MOB4SI,1,base,357937,12,0.0951,1.1412,0.1426,2026-11-12
